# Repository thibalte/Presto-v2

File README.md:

# Presto v2

*The project is currently in development, this repo is not complete yet.*

Presto is an open-source vector plotter designed to handle 70*100cm stock paper. It features a universal gripper to accomodate any tools from super-thin pencils to large paintbrushes.

Updates in v2:

- upgraded hardware for easy and fast (dis)assembly
- easy electronics, no need for 2 arduinos, servo is driven via a small ATTiny chip as slave
- host software for auto/manual printing, on-the-fly G-Code generation
- smaller part count, better integration of components: faster build, simpler manufacturing

## TODO

- design arduino shield PCB including 2 stepper drivers, 1 ATTiny45 to avoid the cable salad and don't have a slave board
- test clip-in system for shafts in side frames instead of current pressure screws, test plywood flex

## Get Started

go to the [How-To](howto.md).

## References

- [dented gear generation](http://hessmer.org/gears/InvoluteSpurGearBuilder.html).

## Thanks

Improvements on side frames and x-carriage thanks to Matt Maurer, Fabian Ritzi, Kevin Rentz @ Hyperwerk, Basel CH.

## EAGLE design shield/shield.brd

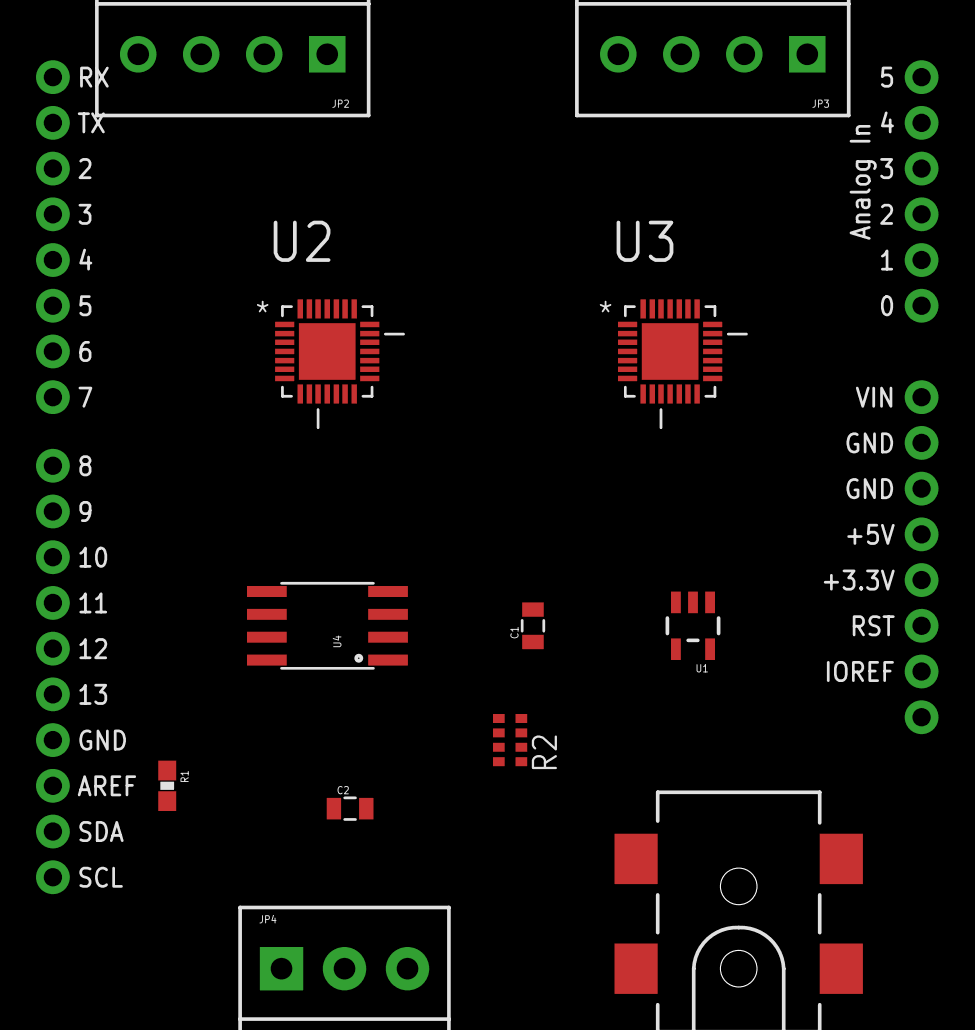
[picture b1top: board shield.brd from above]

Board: 2 copper layers, 13 parts (0 on the bottom side), 20 nets, no tracks yet.

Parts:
C1: 2.2uF; 0805
C2: 1.0uF; 0805
J1: ARDUINO_R3_SHIELD; UNO_R3_SHIELD
JP1: 5.5x2.1mm Barrel; POWER_JACK_SMD
JP2, JP3: SCREWTERMINAL-3.5MM-4
JP4: SCREWTERMINAL-3.5MM-3
R1: 10K; 0603-RES
R2: POTENTIOMETER; 0603-ARV
U1: SOT23-5
U2, U3: A4988SETTR-T; QFN50P500X500X100-29N
U4: Tiny45-20-SMT; SO08-EIAJ

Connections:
5V: C1.1, C2.1, JP4.2, R2.1, U1.5, U2.8, U3.8, U4.8
12V: JP1.VIN0, U1.1, U1.3, U2.15, U3.15
GND: C1.2, C2.2, J1.GND@0, JP1.P$4, JP4.3, R1.2, R2.2, U1.2, U2.18, U3.18, U4.4
unnamed: JP2.1, U2.24
unnamed: JP2.2, U2.21
unnamed: JP2.3, U2.26
unnamed: JP2.4, U2.1
unnamed: JP3.1, U3.24
unnamed: JP3.2, U3.21
unnamed: JP3.3, U3.26
unnamed: JP3.4, U3.1
unnamed: J1.D2, U2.16
unnamed: J1.D5, U2.19
unnamed: J1.D3, U3.16
unnamed: J1.D6, U3.19
unnamed: J1.D13, R1.1, U4.5
unnamed: JP4.1, U4.6
unnamed: R2.3, R2.4, R2.5, R2.6, R2.7, R2.8, U4.7
VBB1: U2.22, U3.22
VBB2: U2.28, U3.28

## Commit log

2015-02-20 added bom
2015-02-20 edited BOM
2015-02-24 added new global assembly, edited readme, bom
2015-02-24 added servo controller code and schematics
2015-02-24 moved folder structure
2015-02-24 added description to servo controller firmware
2015-02-24 updated readme with warning
2015-02-25 added GRBL config and edited servo controller firmware
2015-02-25 edited readme
2015-02-25 added howto.md
2015-02-25 started working on the design of the arduino shield pcb
2015-02-25 worked on the schematics of the shield, corrected a4988 wiring
2015-03-01 added Mission Control printing client, temporary screws list
2015-03-03 started doc FR
2015-03-03 corrected relative paths in doc image links
2015-03-03 corrected doc layout+
2015-03-03 added doc fr
2015-03-03 corrected images in doc fr
2015-03-03 corrected
2015-03-03 changed files from jpg to png
2015-03-03 edited md
2015-03-04 added tools
2015-03-04 edited doc fr
2015-03-04 fixed typos
2015-03-04 corrected numbering in doc fr
2015-03-04 typos
2015-03-04 added ftdi driver install in doc fr
2015-03-05 added arduino controller
2015-03-08 added assembly image
2015-03-08 cleanup and updated image with pen carriage ion wrong side

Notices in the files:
parts and their libraries:
SparkFun-Boards: Licensing: Creative Commons ShareAlike 4.0 International - https://creativecommons.org/licenses/by-sa/4.0
